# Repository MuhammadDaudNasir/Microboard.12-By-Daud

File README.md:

# Microboard.12-By-Daud
a simple micro board for hack club

THIS PROJECT IS OPENSOURCE, YOU CAN USE THE CODE AS YOU WISH.
Desinged for Hackclub

This is a simple pcb with a fusion 360 .step file to house a macropad.

*what does it do?*

well it can be customised to your liking, ex: Ctrl, Home, Pg up, etc.

this is meant to be a simple project to enhance my skills in areas like CAD and pcb desinging.
thanks for Hackclub's Amazing documentation to help me during the making of the macropad.

https://hackpad.hackclub.com/guide

i will be updating this Repo as i make further developments when i order the parts :)

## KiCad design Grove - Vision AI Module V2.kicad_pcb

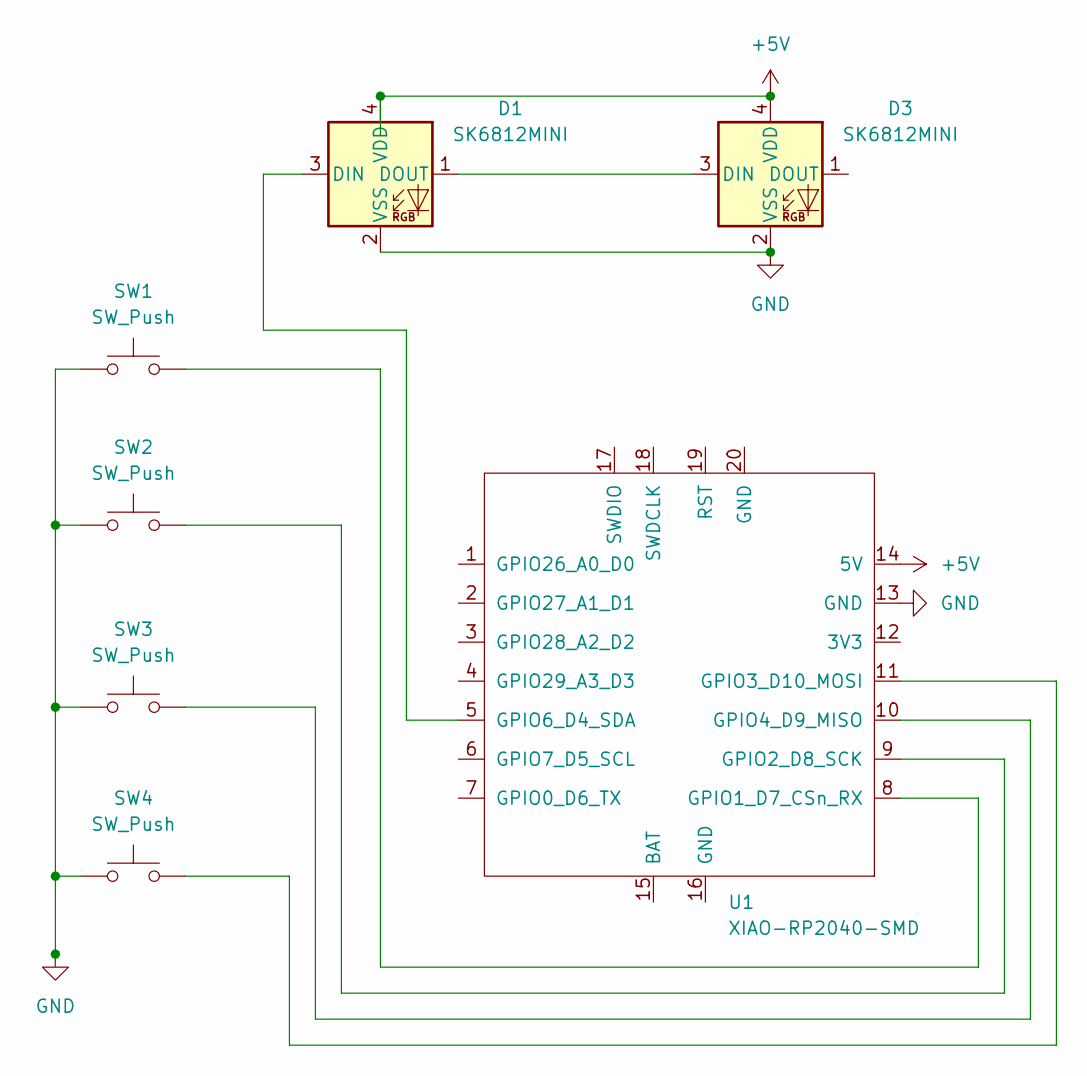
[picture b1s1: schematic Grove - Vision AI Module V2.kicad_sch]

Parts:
D1, D3: SK6812MINI; LED_SK6812MINI_PLCC4_3.5x3.5mm_P1.75mm
SW1, SW2, SW3, SW4: SW_Push; SW_Cherry_MX_1.00u_PCB
U1: XIAO-RP2040-SMD; XIAO-RP2040-DIP

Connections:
+5V: D1.4 (VDD), D3.4 (VDD), U1.14 (5V)
GND: D1.2 (VSS), D3.2 (VSS), SW1.2, SW2.2, SW3.1, SW4.1, U1.13 (GND)
unnamed: D1.3 (DIN), U1.5 (GPIO6_D4_SDA)
unnamed: D1.1 (DOUT), D3.3 (DIN)
unnamed: SW1.1, U1.8 (GPIO1_D7_CSn_RX)
unnamed: SW2.1, U1.9 (GPIO2_D8_SCK)
unnamed: SW4.2, U1.11 (GPIO3_D10_MOSI)
unnamed: SW3.2, U1.10 (GPIO4_D9_MISO)

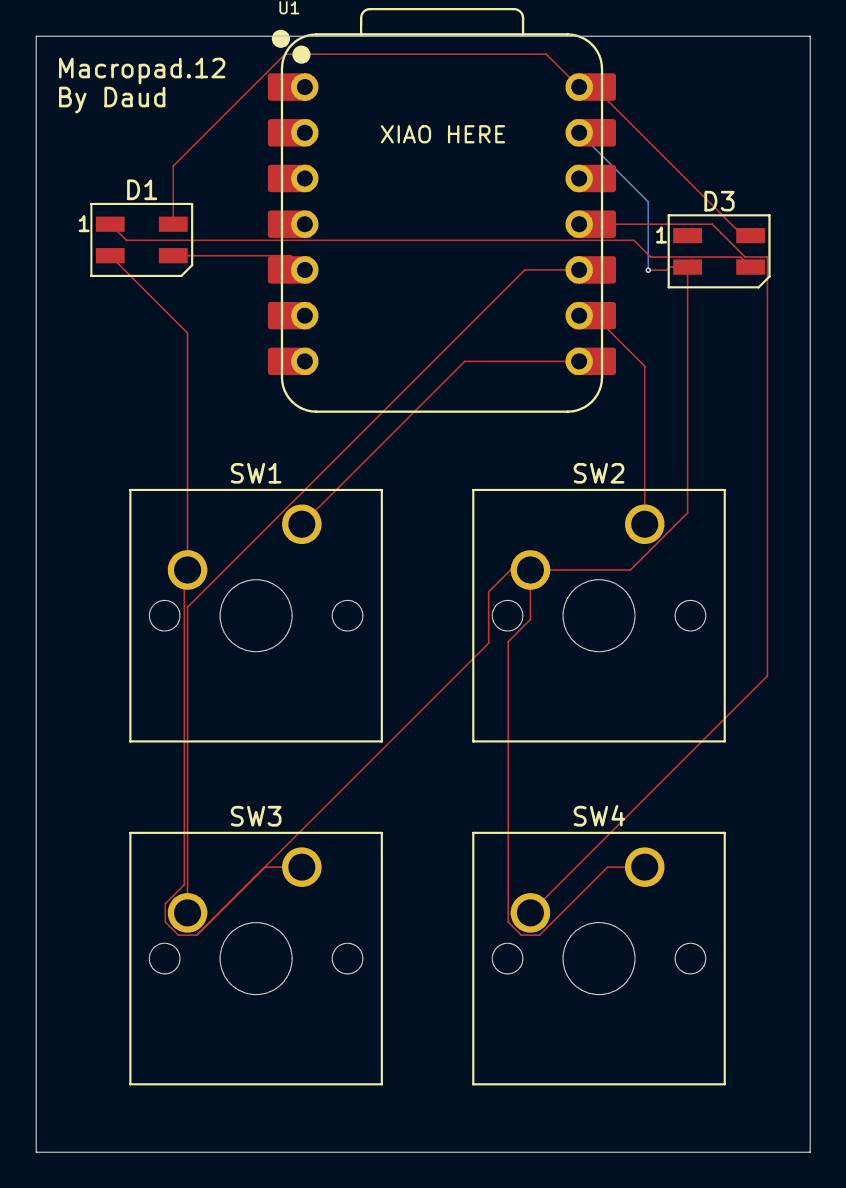
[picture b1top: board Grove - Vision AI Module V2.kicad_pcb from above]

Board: 4 copper layers, 43.0 x 62.0 mm, 7 parts (0 on the bottom side), 8 nets.
